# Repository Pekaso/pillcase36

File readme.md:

A Development Keyboard for ARM Firmware with Blackpill STM32F103

# Features
 - 6 x 6 ortholinear
 - Blackpill STM32F103
 - TRRS Jack
 - External EEPROM
 - Many Test pin (I/O, I2C, UART)

# More Information
See Self-Made Keyboards in Japan Discord Server

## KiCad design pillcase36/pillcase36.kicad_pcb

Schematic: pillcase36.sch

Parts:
0.1u1: C; C_0603
D1, D2, D3, D4, D5, D6, D7, D8, D9, D10, D11, D12, D13, D14, D15, D16, D17, D18, D19, D20, D21, D22, D23, D24, D25, D26, D27, D28, D29, D30, D31, D32, D33, D34, D35, D36: D; Diode_SMD_THT_N
J1: AudioJack4_Ground; trrs_jack_aki_flip
JP13, JP14: SolderJumper_2_Bridged; JP
R1, R2: 10K; Resister_SMD_THT_N
SW1, SW2, SW3, SW4, SW5, SW6, SW7, SW8, SW9, SW10, SW11, SW12, SW13, SW14, SW15, SW16, SW17, SW18, SW19, SW20, SW21, SW22, SW23, SW24, SW25, SW26, SW27, SW28, SW29, SW30, SW31, SW32, SW33, SW34, SW35, SW36: SW_Push; key_switch_mx
SW37: SW_Push; SW_PUSH_6mm_h5mm
TP1: B13; Measurement_Point_Round-TH_Small
TP2: B15; Measurement_Point_Round-TH_Small
TP3: A9; Measurement_Point_Round-TH_Small
TP4: A11; Measurement_Point_Round-TH_Small
TP5: A15; Measurement_Point_Round-TH_Small
TP6: B4; Measurement_Point_Round-TH_Small
TP7: B6; Measurement_Point_Round-TH_Small
TP8: B12; Measurement_Point_Round-TH_Small
TP9: B14; Measurement_Point_Round-TH_Small
TP10: A8; Measurement_Point_Round-TH_Small
TP11: A10; Measurement_Point_Round-TH_Small
TP12: A12; Measurement_Point_Round-TH_Small
TP13: B3; Measurement_Point_Round-TH_Small
TP14: B5; Measurement_Point_Round-TH_Small
TP15: B7; Measurement_Point_Round-TH_Small
TP16: B11; Measurement_Point_Round-TH_Small
TP17: B1; Measurement_Point_Round-TH_Small
TP18: A7; Measurement_Point_Round-TH_Small
TP19: A5; Measurement_Point_Round-TH_Small
TP20: A3; Measurement_Point_Round-TH_Small
TP21: A1; Measurement_Point_Round-TH_Small
TP22: C13; Measurement_Point_Round-TH_Small
TP23: B8; Measurement_Point_Round-TH_Small
TP24: B10; Measurement_Point_Round-TH_Small
TP25: B0; Measurement_Point_Round-TH_Small
TP26: A6; Measurement_Point_Round-TH_Small
TP27: A4; Measurement_Point_Round-TH_Small
TP28: A2; Measurement_Point_Round-TH_Small
TP29: A0; Measurement_Point_Round-TH_Small
TP30: B9; Measurement_Point_Round-TH_Small
TP31: R1; Measurement_Point_Round-TH_Small
TP32: R2; Measurement_Point_Round-TH_Small
U1: BlackPill
U2: 24LC00; SOIC-8-N

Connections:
COL0: SW1.1, SW2.1, SW3.1, SW4.1, SW5.1, SW6.1, TP29.1, U1.23
COL1: SW7.1, SW8.1, SW9.1, SW10.1, SW11.1, SW12.1, TP21.1, U1.24
COL2: SW13.1, SW14.1, SW15.1, SW16.1, SW17.1, SW18.1, TP28.1, U1.25
COL3: SW19.1, SW20.1, SW21.1, SW22.1, SW23.1, SW24.1, TP20.1, U1.26
COL4: SW25.1, SW26.1, SW27.1, SW28.1, SW29.1, SW30.1, TP27.1, U1.27
COL5: SW31.1, SW32.1, SW33.1, SW34.1, SW35.1, SW36.1, TP19.1, U1.28
GND: J1.S, U1.17, U1.18, U2.1 (A0), U2.2 (A1), U2.3 (A2), U2.4 (GND), U2.7 (WP); also elsewhere on the board
unnamed: D1.2, SW1.2
unnamed: D2.2, SW2.2
unnamed: D3.2, SW3.2
unnamed: D4.2, SW4.2
unnamed: D5.2, SW5.2
unnamed: D6.2, SW6.2
unnamed: D7.2, SW7.2
unnamed: D8.2, SW8.2
unnamed: D9.2, SW9.2
unnamed: D10.2, SW10.2
unnamed: D11.2, SW11.2
unnamed: D12.2, SW12.2
unnamed: D13.2, SW13.2
unnamed: D14.2, SW14.2
unnamed: D15.2, SW15.2
unnamed: D16.2, SW16.2
unnamed: D17.2, SW17.2
unnamed: D18.2, SW18.2
unnamed: D19.2, SW19.2
unnamed: D20.2, SW20.2
unnamed: D21.2, SW21.2
unnamed: D22.2, SW22.2
unnamed: D23.2, SW23.2
unnamed: D24.2, SW24.2
unnamed: D25.2, SW25.2
unnamed: D26.2, SW26.2
unnamed: D27.2, SW27.2
unnamed: D28.2, SW28.2
unnamed: D29.2, SW29.2
unnamed: D30.2, SW30.2
unnamed: D31.2, SW31.2
unnamed: D32.2, SW32.2
unnamed: D33.2, SW33.2
unnamed: D34.2, SW34.2
unnamed: D35.2, SW35.2
unnamed: D36.2, SW36.2
unnamed 43: J1.R1; also elsewhere on the board
unnamed 44: J1.R2; also elsewhere on the board
unnamed: TP3.1, U1.6
unnamed: TP4.1, U1.8
unnamed: TP5.1, U1.10
unnamed: TP6.1, U1.12
unnamed: TP10.1, U1.5
unnamed: TP11.1, U1.7
unnamed: TP12.1, U1.9
unnamed: TP13.1, U1.11
unnamed: TP14.1, U1.13
unnamed: TP17.1, U1.32
unnamed: TP18.1, U1.30
unnamed: TP22.1, U1.21
unnamed: TP23.1, U1.19
unnamed: TP25.1, U1.31
unnamed: TP26.1, U1.29
unnamed: TP30.1, U1.20
RESET: U1.22; also elsewhere on the board
ROW0: D1.1, D7.1, D13.1, D19.1, D25.1, D31.1, TP24.1, U1.33
ROW1: D2.1, D8.1, D14.1, D20.1, D26.1, D32.1, TP16.1, U1.34
ROW2: D3.1, D9.1, D15.1, D21.1, D27.1, D33.1, TP8.1, U1.1
ROW3: D4.1, D10.1, D16.1, D22.1, D28.1, D34.1, TP1.1, U1.2
ROW4: D5.1, D11.1, D17.1, D23.1, D29.1, D35.1, TP9.1, U1.3
ROW5: D6.1, D12.1, D18.1, D24.1, D30.1, D36.1, TP2.1, U1.4
SCL1: R1.2, TP7.1, U1.14, U2.6 (SCL); also elsewhere on the board
SDA1: R2.2, TP15.1, U1.15, U2.5 (SDA); also elsewhere on the board
VCC: J1.T, R1.1, R2.1, U1.16, U2.8 (VCC); also elsewhere on the board

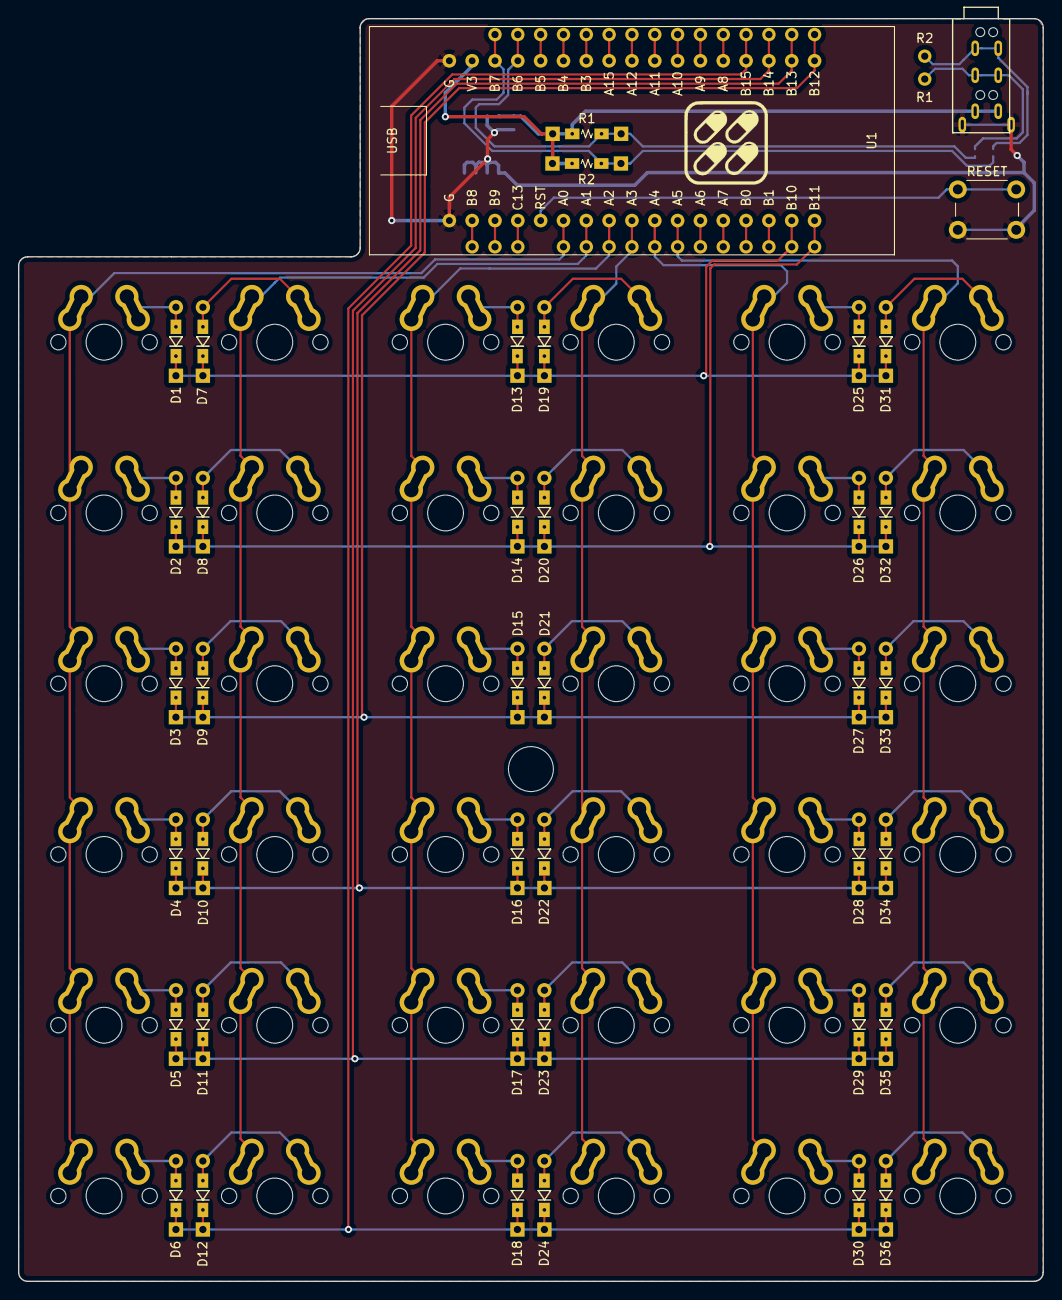
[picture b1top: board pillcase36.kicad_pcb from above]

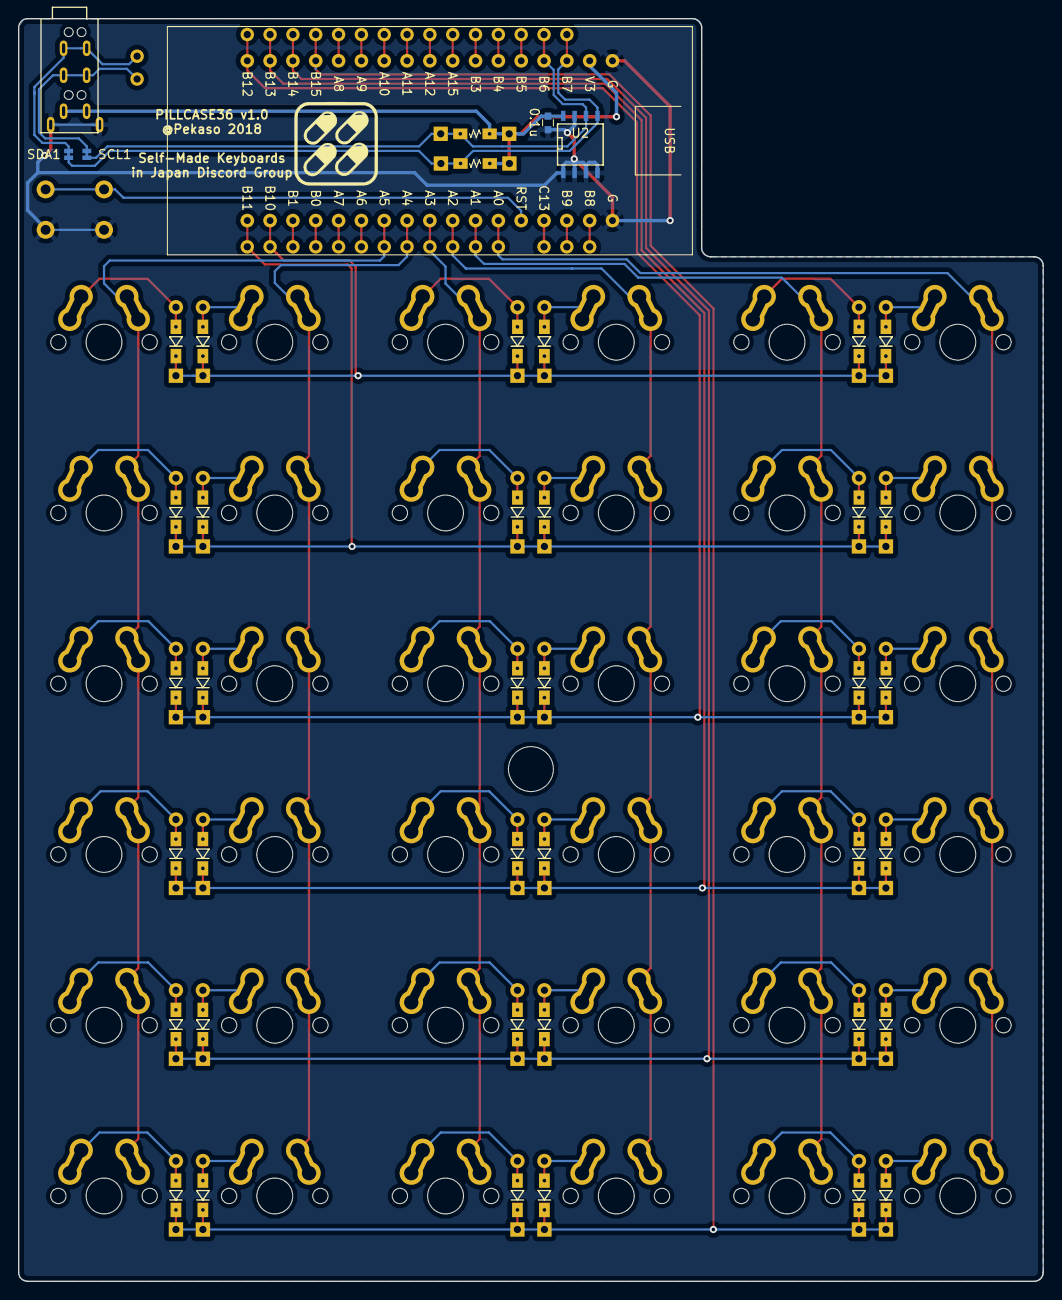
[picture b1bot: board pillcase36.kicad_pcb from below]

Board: 2 copper layers, 114.0 x 140.5 mm, 113 parts (4 on the bottom side), 71 nets.

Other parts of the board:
0.1u: C; C_0603
R1#2: R1; Measurement_Point_Round-TH_Small
R2#2: R2; Measurement_Point_Round-TH_Small
RESET: SW_Push; SW_PUSH_6mm_h5mm
SCL1 : SolderJumper_2_Bridged; JP
SDA1: SolderJumper_2_Bridged; JP

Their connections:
GND: 0.1u.2, RESET.2; also elsewhere on the board
unnamed 43: R1#2.1, SCL1.2; also elsewhere on the board
unnamed 44: R2#2.1, SDA1.2; also elsewhere on the board
RESET: RESET.1; also elsewhere on the board
SCL1: SCL1.1; also elsewhere on the board
SDA1: SDA1.1; also elsewhere on the board
VCC: 0.1u.1; also elsewhere on the board

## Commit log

2018-08-27 Add Schematic
2018-08-30 add PCB
2018-08-31 Make a case directory
2018-08-31 Oops
2018-08-31 Quick trace cleanup
    - Aesthetic changes
    - Via reduction
    - Reduction of right angle traces
    - Move traces away from edge
2018-08-31 Reroute row/col breakout
2018-08-31 Fix some DRC errors
2018-08-31 Tune routing further, fix silkscreen label positions
2018-08-31 Finish reroute, ready pull request
2018-08-31 Remove case files directory for now
2018-08-31 main_v1.0 release
2018-08-31 Straighten a few squiggly traces
    Where the jumpers used to be
2018-09-04 PCB v1.0.1 Release
2018-09-17 add MIT License
